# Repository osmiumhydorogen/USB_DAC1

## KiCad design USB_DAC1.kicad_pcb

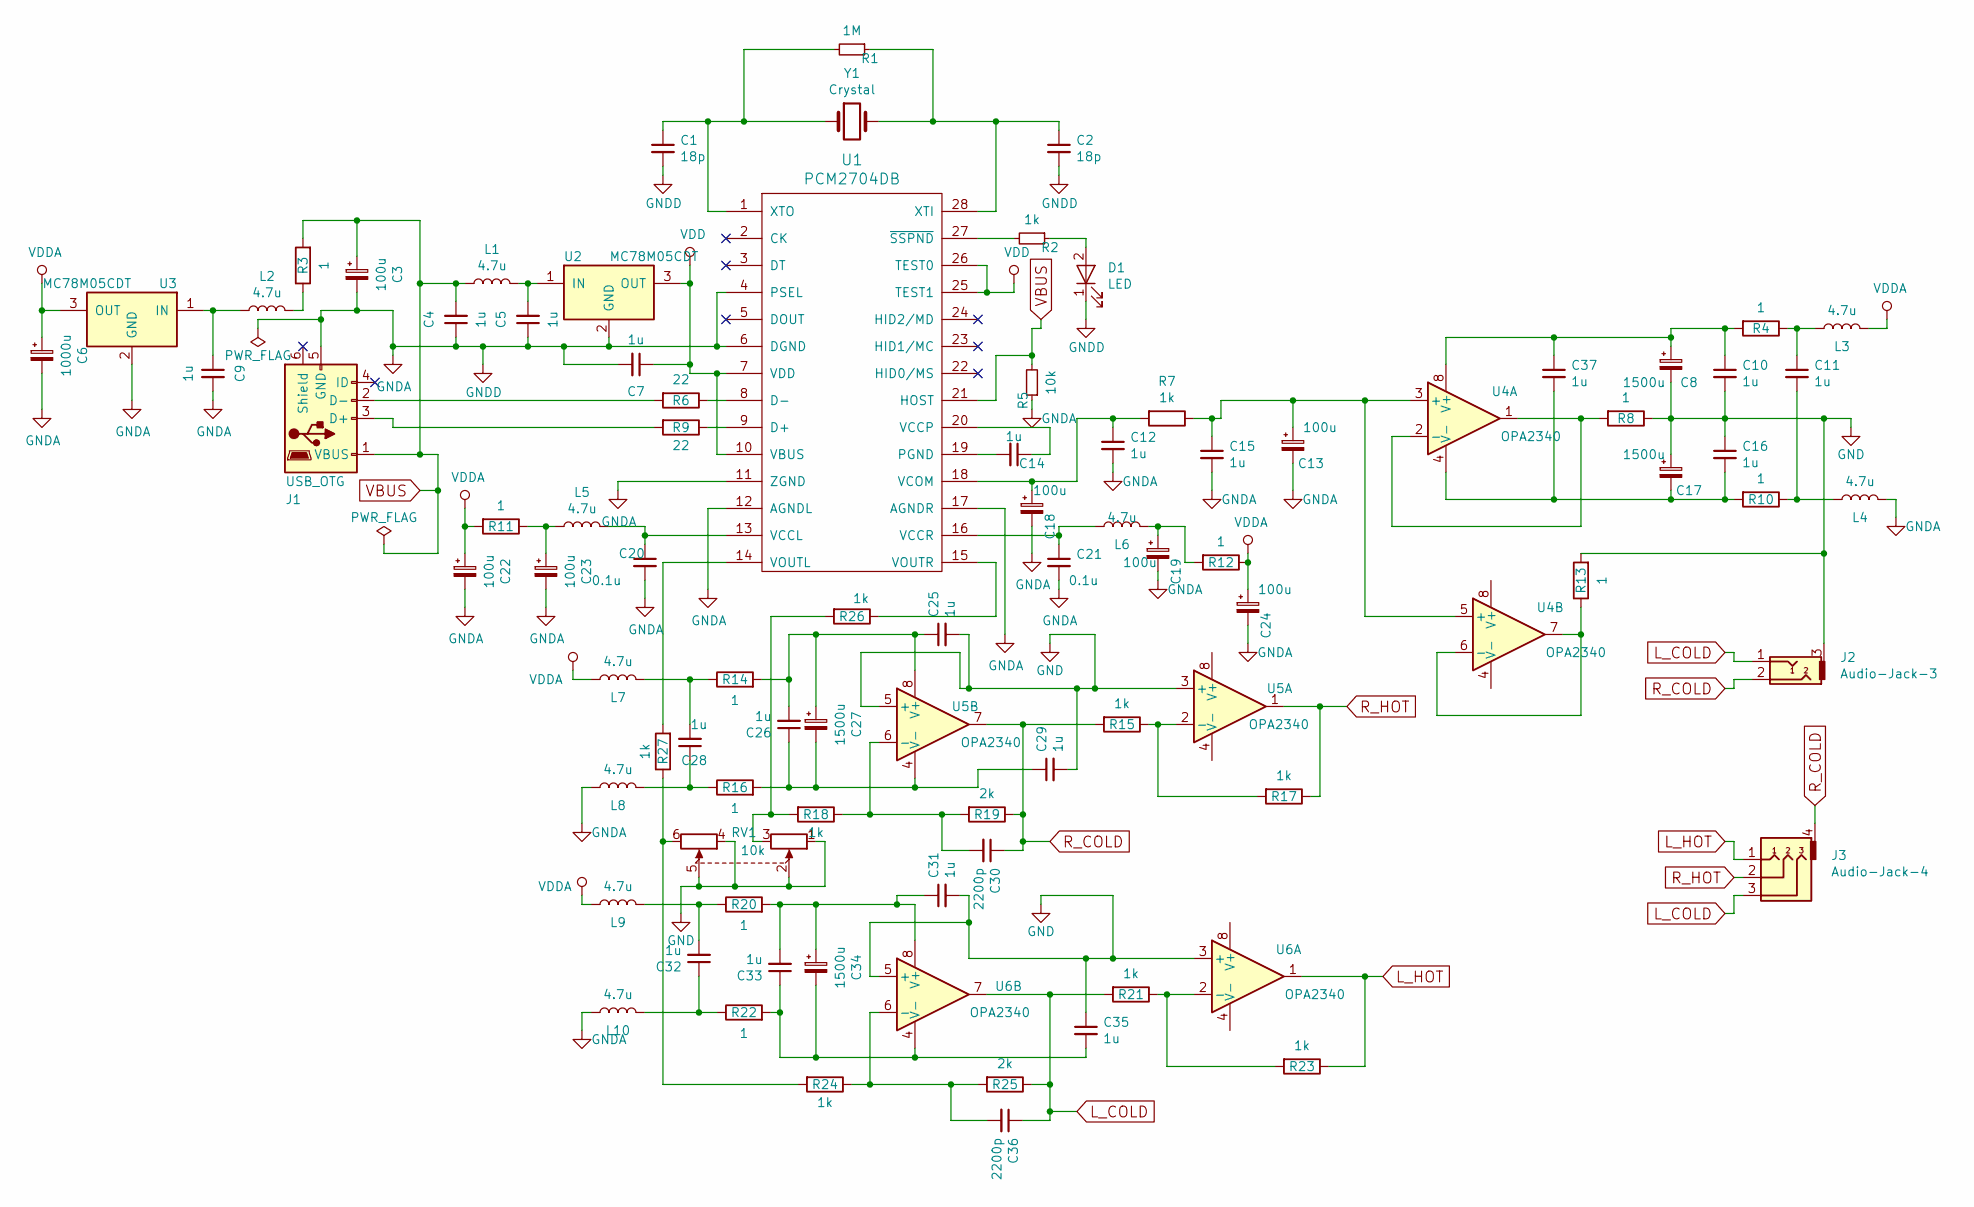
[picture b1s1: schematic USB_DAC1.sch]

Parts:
C1, C2: 18p; Pin_Header_Straight_1x02_Pitch2.54mm
C3, C13, C18, C19, C22, C23, C24: 100u; C1V8
C4, C5, C7, C9, C10, C11, C12, C14, C15, C16, C25, C26, C28, C29, C31, C32, C33, C35, C37: 1u; C_0805_HandSoldering
C6: 1000u; C2V8
C8, C17, C27, C34: 1500u; C2V8
C20, C21: 0.1u; C_0805_HandSoldering
C30, C36: 2200p; Pin_Header_Straight_1x02_Pitch2.54mm
D1: LED; LED_0603
J1: USB_OTG; USB_Micro-B_Molex_47346-0001
J2: Audio-Jack-3; 35_TRS
J3: Audio-Jack-4; TRRS_1
L1, L2, L3, L4, L5, L6, L7, L8, L9, L10: 4.7u; INDUCTOR_V
R1: 1M; R3
R2, R7, R15, R17, R18, R21, R23, R24, R26, R27: 1k; R3
R3, R4, R8, R10, R11, R12, R13, R14, R16, R20, R22: 1; R3
R5: 10k; R3
R6, R9: 22; R3
R19, R25: 2k; R3
RV1: 10k; Potentiometer_Alps_RK097_Double_Vertical
U1: PCM2704DB; SSOP-28_5.3x10.2mm_Pitch0.65mm
U2, U3: MC78M05CDT; TO-252-2Lead
U4, U5, U6: OPA2340; DIP-8_W7.62mm
Y1: Crystal; Crystal_HC18-U_Vertical

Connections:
GND: C8.2, C10.2, C16.1, C17.1, C25.2, C29.2, C31.2, C35.1, J2.3, R8.1, R13.2, RV1.1, RV1.2, RV1.4, RV1.5, U5.3 (+), U5.5 (+), U6.3 (+), U6.5 (+)
GNDA: C1.2, C2.2, C3.2, C4.1, C5.1, C6.2, C7.2, C9.2, C12.2, C13.2, C15.2, C18.2, C19.2, C20.2, C21.2, C22.2, C23.2, C24.2, D1.1 (K), J1.5 (GND), L4.2, L8.1, L10.1, R5.1, U1.4 (PSEL), U1.6 (DGND), U1.11 (ZGND), U1.12 (AGNDL), U1.17 (AGNDR), U2.2 (GND), U3.2 (GND)
L_COLD: C36.1, J2.1, J3.3, R21.2, R25.1, U6.7
L_HOT: J3.1, R23.1, U6.1
unnamed: C1.1, R1.2, U1.1 (XTO), Y1.1
unnamed: C2.1, R1.1, U1.28 (XTI), Y1.2
unnamed: C5.2, L1.2, U2.1 (IN)
unnamed: C9.1, L2.1, U3.1 (IN)
unnamed: C8.1, C10.1, C37.1, R4.2, U4.8 (V+)
unnamed: C11.1, L3.1, R4.1
unnamed: C11.2, L4.1, R10.1
unnamed: C12.1, C18.1, R7.2, U1.18 (VCOM)
unnamed: C13.1, C15.1, R7.1, U4.3 (+), U4.5 (+)
unnamed: C14.1, U1.20 (VCCP)
unnamed: C14.2, U1.19 (PGND)
unnamed: C16.2, C17.2, C37.2, R10.2, U4.4 (V-)
unnamed: C19.1, L6.2, R12.2
unnamed: C20.1, L5.2, U1.13 (VCCL)
unnamed: C21.1, L6.1, U1.16 (VCCR)
unnamed: C23.1, L5.1, R11.1
unnamed: C25.1, C26.2, C27.1, R14.2, U5.8 (V+)
unnamed: C26.1, C27.2, C29.1, R16.2, U5.4 (V-)
unnamed: C28.1, L8.2, R16.1
unnamed: C28.2, L7.2, R14.1
unnamed: C30.2, R18.1, R19.2, U5.6 (-)
unnamed: C31.1, C33.2, C34.1, R20.2, U6.8 (V+)
unnamed: C32.1, L10.2, R22.1
unnamed: C32.2, L9.2, R20.1
unnamed: C33.1, C34.2, C35.2, R22.2, U6.4 (V-)
unnamed: C36.2, R24.1, R25.2, U6.6 (-)
unnamed: D1.2 (A), R2.1
unnamed: J1.2 (D-), R6.2
unnamed: J1.3 (D+), R9.2
unnamed: L2.2, R3.1
unnamed: R2.2, U1.27 (~SSPND)
unnamed: R6.1, U1.8 (D-)
unnamed: R8.2, U4.1, U4.2 (-)
unnamed: R9.1, U1.9 (D+)
unnamed: R13.1, U4.6 (-), U4.7
unnamed: R15.1, R17.2, U5.2 (-)
unnamed: R18.2, R26.2, RV1.3
unnamed: R21.1, R23.2, U6.2 (-)
unnamed: R24.2, R27.1, RV1.6
unnamed: R26.1, U1.15 (VOUTR)
unnamed: R27.2, U1.14 (VOUTL)
R_COLD: C30.1, J2.2, J3.4, R15.2, R19.1, U5.7
R_HOT: J3.2, R17.1, U5.1
VBUS: C3.1, C4.2, J1.1 (VBUS), L1.1, R3.2, R5.2, U1.21 (HOST)
VDD: C7.1, U1.7 (VDD), U1.10 (VBUS), U1.25 (TEST1), U1.26 (TEST0), U2.3 (OUT)
VDDA: C6.1, C22.1, C24.1, L3.2, L7.1, L9.1, R11.2, R12.1, U3.3 (OUT)

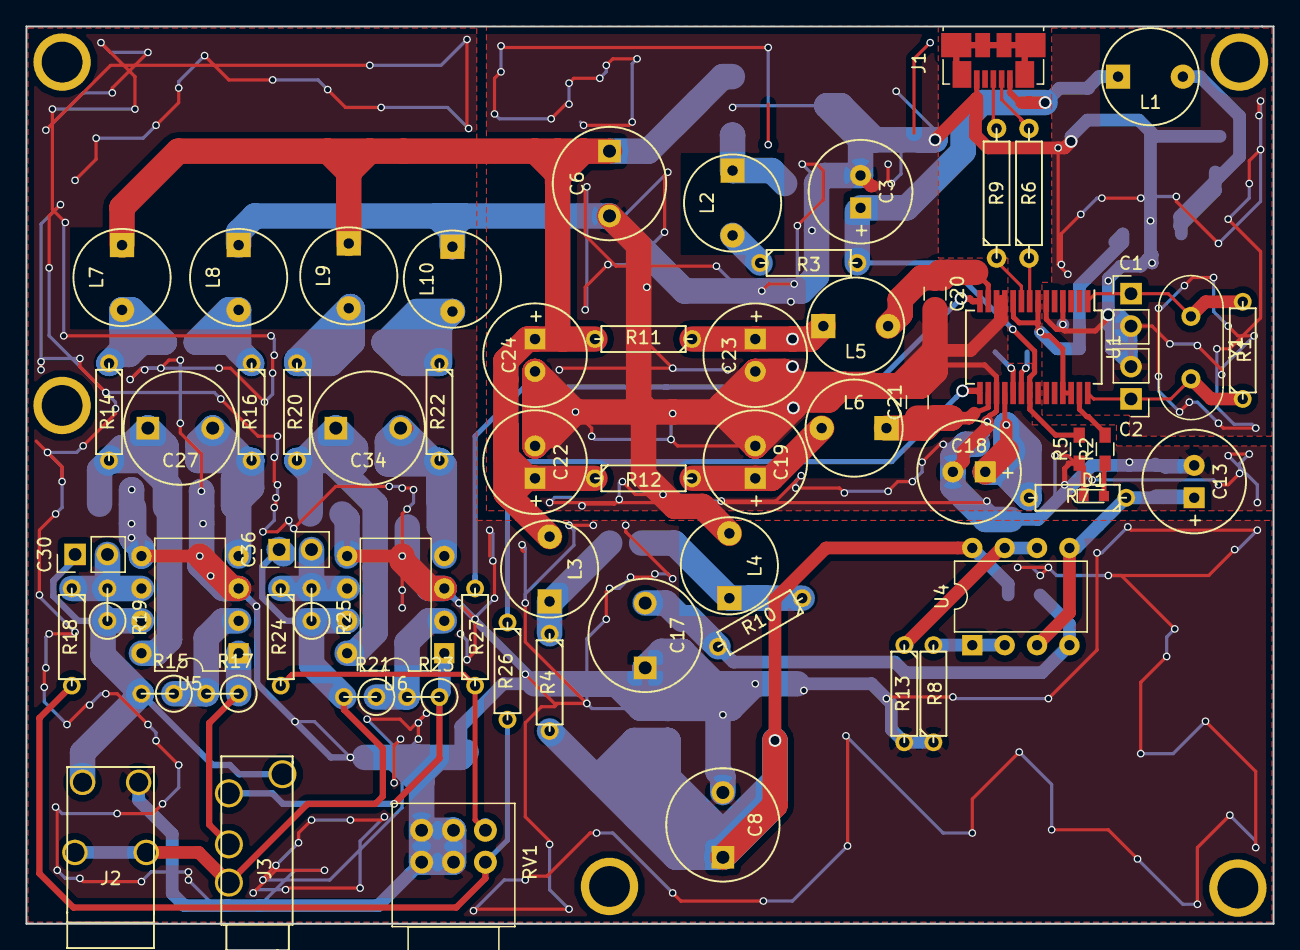
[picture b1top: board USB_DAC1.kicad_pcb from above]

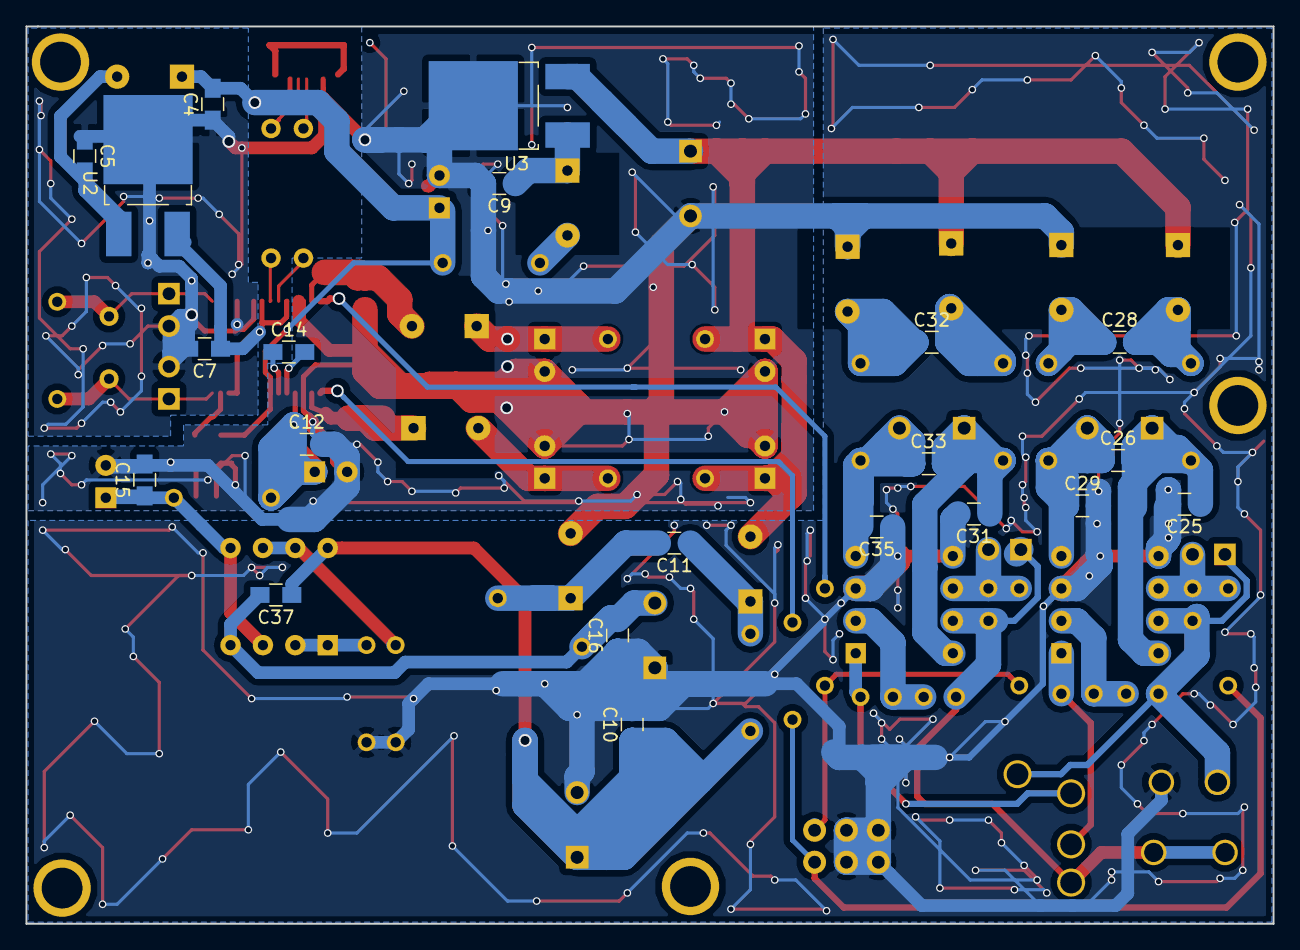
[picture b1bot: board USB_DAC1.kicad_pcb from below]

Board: 2 copper layers, 97.8 x 70.4 mm, 86 parts (21 on the bottom side), 50 nets.

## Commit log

2017-08-28 最初のコミット
2017-11-04 ボードを追加
2017-11-11 C18 C17 C8が干渉してた問題の修正 部品表の追加
